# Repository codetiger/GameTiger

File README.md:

</p>

## About GameTiger Console
A retro-themed gaming console, crafted and tailored exclusively for educational enjoyment. The console boasts a custom-designed printed circuit board (PCB), meticulously created entirely from the ground up, and is centered around the remarkable RP2040 MCU chip. The primary objective of this endeavor is to maintain complete openness, facilitating the exploration of electronic PCB design and the establishment of a platform that fosters the creation of games and emulators on microcontrollers.

<div style="display: flex; justify-content: space-between;">

</div>

## Games
|   |   |
|---|---|
| Snake | 2048 |
|  |  
| Tetris | Minesweeper |
|  | 
| Tic Tac Toe | Ninja Frog |
|  | 

## Software
The software is constructed using the Pico C++ SDK, incorporating essential hardware interfacing functionalities. As an illustration, the well-known Snake game is already available. The following modules are currently available and are continually being developed.

* Operating System Drivers
    * Display driver
    * Button interrupts
    * Battery management system driver
* Framebuffer Library
    * Supports transparency
    * Streaming to display memory using DMA
    * Draw primitives (Line, Rect, Fill Rect)
    * Supports drawing images with alpha channel
* Sprite sheet 
    * Support for sprite sheet 
    * Basic tilemap support
* Font system based on Sprite sheet
* Menu system
    * Games
    * Hardware config
        * Display brightness
        * Display sleep time after inactivity

The software is well optimised to achieve a target of 30 frames per second. The Snake game achieves more than 44 FPS on a default settings without overclocking. 

Hardware V3:

Hardware V2:

Hardware V1:

## Build your favourite games
If you're looking to contribute to the project by developing your own games for the GameTiger console, please refer to our developer guide for detailed instructions.
[Developer's Guide](docs/dev_guide.md)

## To Do
* Add more games
* Design Case in CAD software for 3d printing

## License
The entire project is open-sourced software licensed under the MIT license.

## References
* [Hardware Design with RP2040](https://datasheets.raspberrypi.com/rp2040/hardware-design-with-rp2040.pdf)
* [Minimal RP2040 Board](http://www.technoblogy.com/show?3U75)
* [HAGL Graphics Library](https://github.com/tuupola/hagl)
* [PCB Design for RP2040 youtube video](https://www.youtube.com/watch?v=kcwvuwetgEQ)

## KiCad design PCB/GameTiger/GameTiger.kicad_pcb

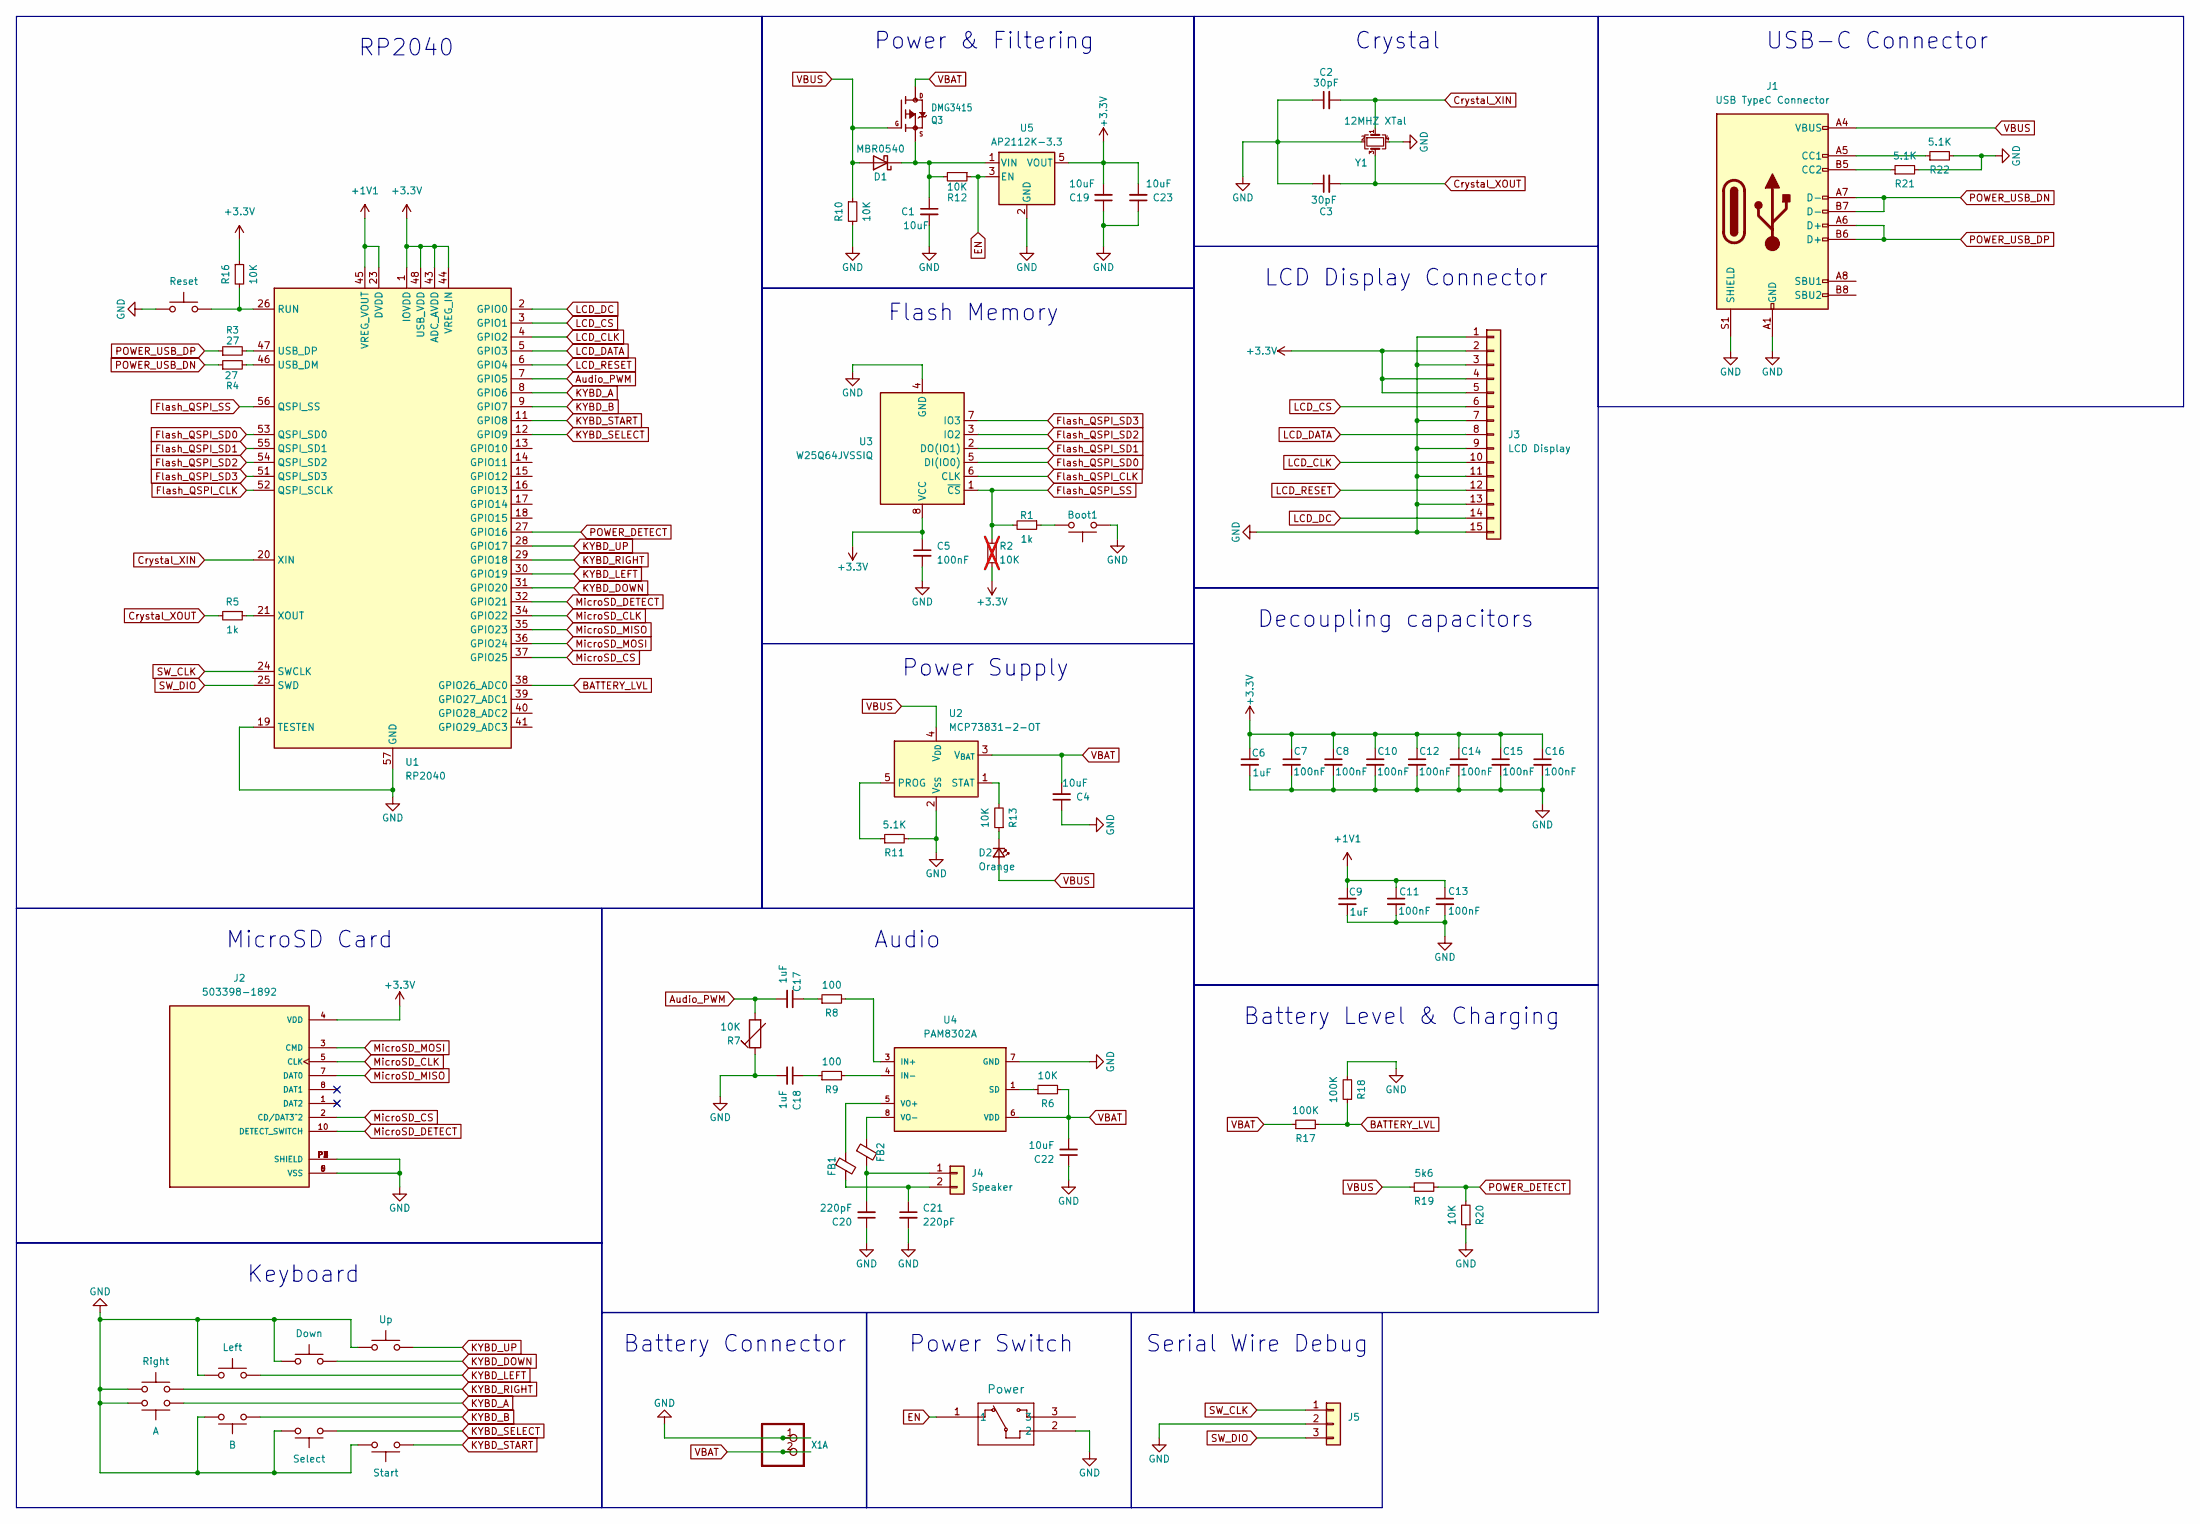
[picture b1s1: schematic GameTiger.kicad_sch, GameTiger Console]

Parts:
A1: A; SW_PUSH-12mm_3DModel; LCSC C411882
B1: B; SW_PUSH-12mm_3DModel; LCSC C411882
Boot1: Boot; SW_SPST_B3U-1000P; Mfr.Part # B3U-1000P; LCSC C231329
C1, C4, C19, C22, C23: 10uF; C_0805_2012Metric; LCSC C15850
C2, C3: 30pF; C_0402_1005Metric; LCSC C1570
C5, C7, C8, C10, C11, C12, C13, C14, C15, C16: 100nF; C_0402_1005Metric; LCSC C1525
C6, C9, C17, C18: 1uF; C_0402_1005Metric; LCSC C52923
C20, C21: 220pF; C_0805_2012Metric; LCSC C107145
D1: MBR0540; D_SOD-123; Manuf. Part # MBR0540; LCSC C116159
D2: Orange; LED_0402_1005Metric; LCSC C965791
Down1: Down; SW_PUSH-12mm_3DModel; LCSC C411882
FB1, FB2: FerriteBead_Small; Ferrite_0805_2012Metric; Manuf. Part # BLM21BD102SN1D; LCSC C85835
J1: USB TypeC Connector; USB_C_Receptacle_HRO_TYPE-C-31-M-12; Manuf. Part # GT-USB-7010ASV; LCSC C2988369
J2: 503398-1892; MOLEX_503398-1892; Manuf. Part # 5033981892; LCSC C428492
J3: LCD Display; TE_1-1734839-5_1x15-1MP_P0.5mm_Horizontal; Manuf. Part # 1-1734839-5; LCSC C262209
J4: Speaker; SolderWire-0.5sqmm_1x02_P4.6mm_D0.9mm_OD2.1mm
J5: Conn_01x03; SolderWire-0.25sqmm_1x03_P4.2mm_D0.65mm_OD1.7mm
Left1: Left; SW_PUSH-12mm_3DModel; LCSC C411882
Power1: Power; MK-12C02-G020_GSW; Manuf. Part # MK-12C02-G020; LCSC C963206
Q3: DMG3415; SOT-23; Manuf. Part # DMG3415U-7; LCSC C96616
R1, R5: 1k; R_0402_1005Metric; LCSC C11702
R2: 10K; R_0402_1005Metric; LCSC C25744; not fitted
R3, R4: 27; R_0402_1005Metric; LCSC C25190
R6, R10, R12, R13, R16, R20: 10K; R_0402_1005Metric; LCSC C25744
R7: 10K; Potentiometer_Bourns_TC33X_Vertical; Manuf. Part # TC33X-2-103E; LCSC C719176
R8, R9: 100; R_0402_1005Metric; LCSC C25076
R11, R21, R22: 5.1K; R_0402_1005Metric; LCSC C25905
R17, R18: 100K; R_0402_1005Metric; LCSC C25741
R19: 5k6; R_0402_1005Metric; LCSC C25908
Reset1: Reset; SW_SPST_B3U-1000P; Mfr.Part # B3U-1000P; LCSC C231329
Right1: Right; SW_PUSH-12mm_3DModel; LCSC C411882
Select1: Select; SW_TH_Tactile_Omron_B3F-10xx; LCSC C411882
Start1: Start; SW_TH_Tactile_Omron_B3F-10xx; LCSC C411882
U1: RP2040; QFN-56-1EP_7x7mm_P0.4mm_EP3.2x3.2mm; Mfr.Part # RP2040; LCSC C2040
U2: MCP73831-2-OT; SOT-23-5; Manuf. Part # MCP73831T-2ACI/OT; LCSC C424093
U3: W25Q64JVSSIQ; SOIC-8_5.23x5.23mm_P1.27mm; Manuf. Part # W25Q64JVSSIQ; LCSC C179171
U4: PAM8302A; MSOP-8_3x3mm_P0.65mm; Manuf. Part # PAM8302AASCR; LCSC C113367
U5: AP2112K-3.3; SOT_RG1_DIO; Manuf. Part # AP2112K-3.3TRG1; LCSC C51118
Up1: Up; SW_PUSH-12mm_3DModel; LCSC C411882
X1: JST_PH_S2B-PH-SM4-TB_1x02-1MP_P2.00mm_Horizontal; Manuf. Part # S2B-PH-SM4-TB(LF)(SN); LCSC C295747
Y1: 12MHZ XTal; Crystal_SMD_3225-4Pin_3.2x2.5mm; Manuf. Part # X322512MSB4SI; LCSC C9002

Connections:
+1V1: C9.1, C11.1, C13.1, U1.23 (DVDD), U1.45 (VREG_VOUT), U1.50 (DVDD)
+3.3V: C5.1, C6.1, C7.1, C8.1, C10.1, C12.1, C14.1, C15.1, C16.1, C19.2, C23.2, J2.4 (VDD), J3.2, J3.4, J3.5, R2.1, R16.1, U1.1 (IOVDD), U1.10 (IOVDD), U1.22 (IOVDD), U1.33 (IOVDD), U1.42 (IOVDD), U1.43 (ADC_AVDD), U1.44 (VREG_IN), U1.48 (USB_VDD), U1.49 (IOVDD), U3.8 (VCC), U5.5 (VOUT)
Audio_PWM: C17.2, R7.2, U1.7 (GPIO5)
BATTERY_LVL: R17.2, R18.1, U1.38 (GPIO26_ADC0)
Crystal_XIN: C2.2, U1.20 (XIN), Y1.1
Crystal_XOUT: C3.2, R5.2, Y1.3
EN: Power1.1, R12.1, U5.3 (EN)
Flash_QSPI_CLK: U1.52 (QSPI_SCLK), U3.6 (CLK)
Flash_QSPI_SD0: U1.53 (QSPI_SD0), U3.5 (DI(IO0))
Flash_QSPI_SD1: U1.55 (QSPI_SD1), U3.2 (DO(IO1))
Flash_QSPI_SD2: U1.54 (QSPI_SD2), U3.3 (IO2)
Flash_QSPI_SD3: U1.51 (QSPI_SD3), U3.7 (IO3)
Flash_QSPI_SS: R1.2, R2.2, U1.56 (QSPI_SS), U3.1 (~CS)
GND: A1.2, B1.2, Boot1.1, C1.2, C2.1, C3.1, C4.1, C5.2, C6.2, C7.2, C8.2, C9.2, C10.2, C11.2, C12.2, C13.2, C14.2, C15.2, C16.2, C18.2, C19.1, C20.1, C21.2, C22.1, C23.1, Down1.1, J1.A1 (GND), J1.A12 (GND), J1.B1 (GND), J1.B12 (GND), J1.S1 (SHIELD), J2.6 (VSS), J2.9 (VSS), J2.P1 (SHIELD), J2.P2 (SHIELD), J2.P3 (SHIELD), J2.P4 (SHIELD), J3.1, J3.3, J3.7, J3.9, J3.11, J3.13, J3.15, J5.2, Left1.1, Power1.2, R7.1, R10.2, R11.2, R18.2, R20.1, R21.2, R22.2, Reset1.1, Right1.1, Select1.2, Start1.2, U1.19 (TESTEN), U1.57 (GND), U2.2 (V_{SS}), U3.4 (GND), U4.7 (GND), U5.2 (GND), Up1.1, X1.1, Y1.2, Y1.4
KYBD_A: A1.1, U1.8 (GPIO6)
KYBD_B: B1.1, U1.9 (GPIO7)
KYBD_DOWN: Down1.2, U1.31 (GPIO20)
KYBD_LEFT: Left1.2, U1.30 (GPIO19)
KYBD_RIGHT: Right1.2, U1.29 (GPIO18)
KYBD_SELECT: Select1.1, U1.12 (GPIO9)
KYBD_START: Start1.1, U1.11 (GPIO8)
KYBD_UP: U1.28 (GPIO17), Up1.2
LCD_CLK: J3.10, U1.4 (GPIO2)
LCD_CS: J3.6, U1.3 (GPIO1)
LCD_DATA: J3.8, U1.5 (GPIO3)
LCD_DC: J3.14, U1.2 (GPIO0)
LCD_RESET: J3.12, U1.6 (GPIO4)
MicroSD_CLK: J2.5 (CLK), U1.34 (GPIO22)
MicroSD_CS: J2.2 (CD/DAT3^2), U1.37 (GPIO25)
MicroSD_DETECT: J2.10 (DETECT_SWITCH), U1.32 (GPIO21)
MicroSD_MISO: J2.7 (DAT0), U1.35 (GPIO23)
MicroSD_MOSI: J2.3 (CMD), U1.36 (GPIO24)
unnamed: Boot1.2, R1.1
unnamed: C17.1, R8.1
unnamed: C18.1, R9.1
unnamed 35: C1.1, D1.1 (K), R12.2, U5.1 (VIN); also elsewhere on the board
unnamed: D2.1 (K), R13.1
unnamed: J1.A5 (CC1), R22.1
unnamed: J1.B5 (CC2), R21.1
unnamed: C20.2, FB2.2, J4.1
unnamed: C21.1, FB1.2, J4.2
unnamed: R16.2, Reset1.2, U1.26 (RUN)
unnamed: R4.2, U1.46 (USB_DM)
unnamed: R3.2, U1.47 (USB_DP)
unnamed: R5.1, U1.21 (XOUT)
unnamed: R11.1, U2.5 (PROG)
unnamed: R13.2, U2.1 (STAT)
unnamed: R8.2, U4.3 (IN+)
unnamed: R9.2, U4.4 (IN-)
unnamed: R6.1, U4.1 (SD)
unnamed: FB1.1, U4.5 (VO+)
unnamed: FB2.1, U4.8 (VO-)
POWER_DETECT: R19.2, R20.2, U1.27 (GPIO16)
POWER_USB_DN: J1.A7 (D-), J1.B7 (D-), R4.1
POWER_USB_DP: J1.A6 (D+), J1.B6 (D+), R3.1
SW_CLK: J5.1, U1.24 (SWCLK)
SW_DIO: J5.3, U1.25 (SWD)
VBAT: C4.2, C22.2, R6.2, R17.1, U2.3 (V_{BAT}), U4.6 (VDD), X1.2; also elsewhere on the board
VBUS: D1.2 (A), D2.2 (A), J1.A4 (VBUS), J1.A9 (VBUS), J1.B4 (VBUS), J1.B9 (VBUS), R10.1, R19.1, U2.4 (V_{DD}); also elsewhere on the board

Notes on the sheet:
Serial Wire Debug
Battery Connector
Audio
Battery Level & Charging
RP2040
Power Switch
Keyboard
Decoupling capacitors
MicroSD Card
Power Supply
LCD Display Connector
Power & Filtering
Crystal
Flash Memory
USB-C Connector

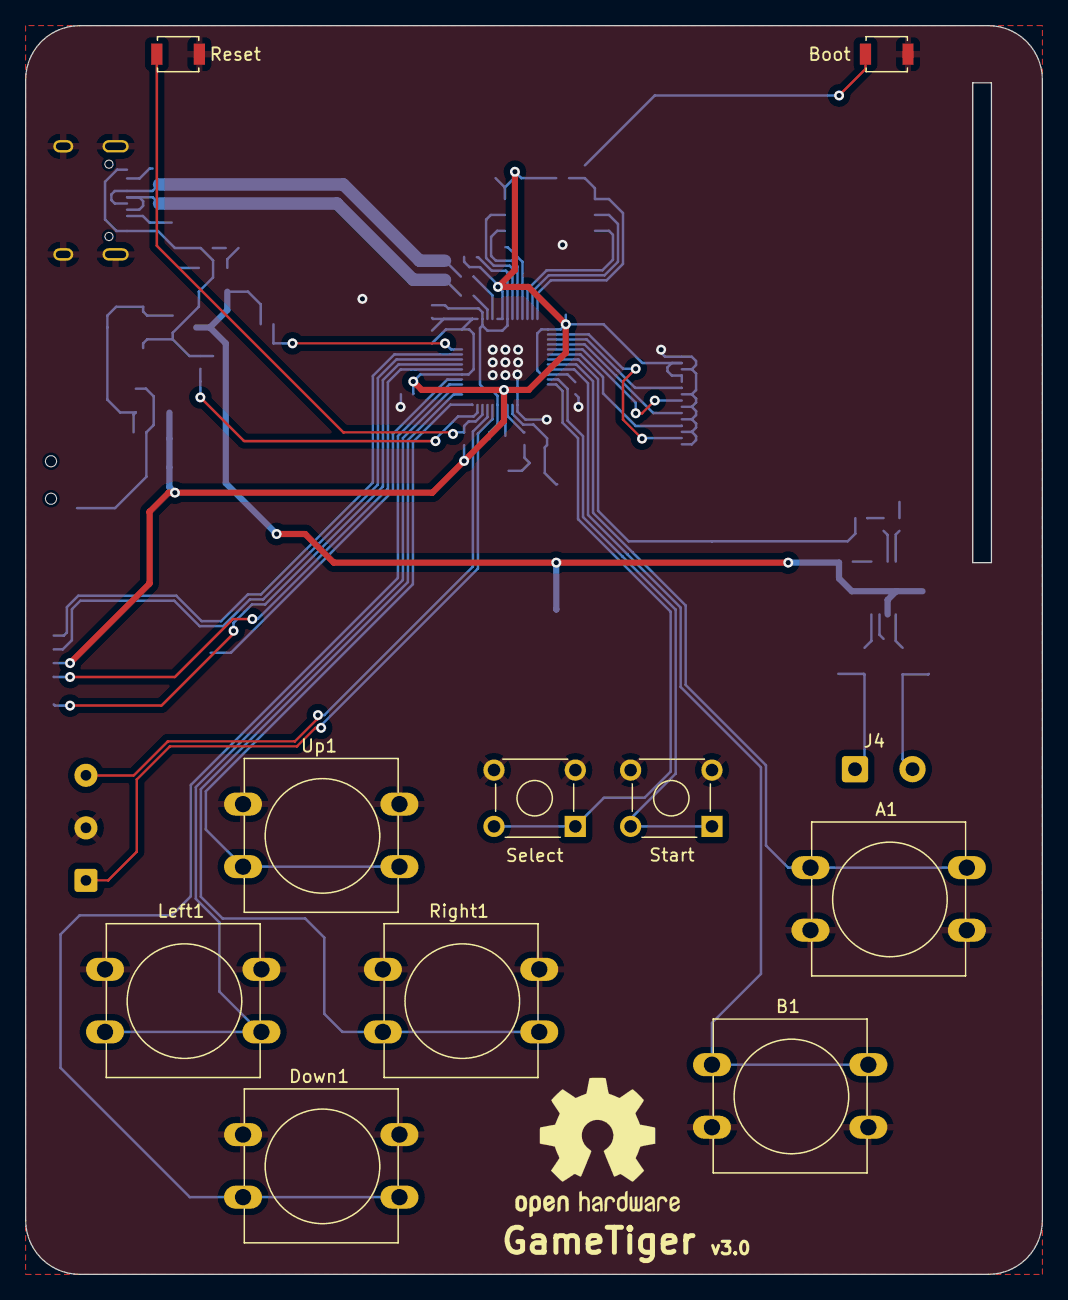
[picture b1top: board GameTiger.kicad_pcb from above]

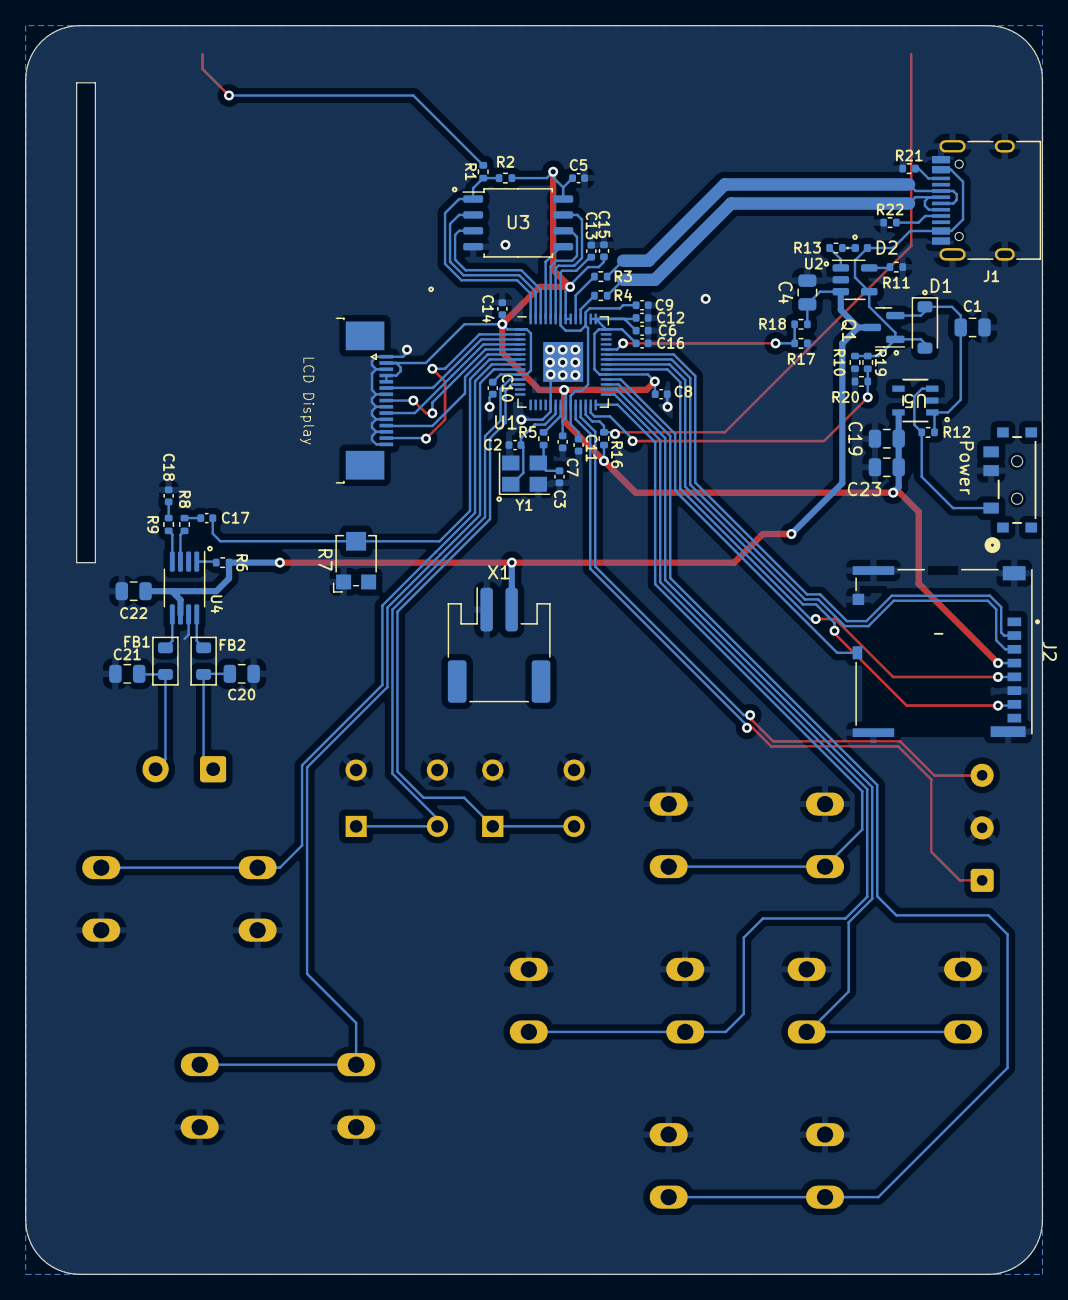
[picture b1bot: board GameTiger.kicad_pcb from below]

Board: 2 copper layers, 81.3 x 99.8 mm, 71 parts (59 on the bottom side), 59 nets.

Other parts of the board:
Q1: DMG3415; SOT-23

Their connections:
unnamed 35: Q1.2 (S); also elsewhere on the board
VBAT: Q1.3 (D); also elsewhere on the board
VBUS: Q1.1 (G); also elsewhere on the board

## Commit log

2022-02-18 Initial Commit with Snake game working
2022-02-18 Fixed support for MacOS
2022-03-08 Added splash, menu and game screen with Snake Game working
2022-03-08 Performance optimisations on image rendering
2022-03-09 Display class performance optimisation. FPS improved from 12 to 22
2022-03-09 Added more info on readme file
2022-03-09 Reduced the image size
2022-03-14 Fixed highscore persistance
2022-03-14 Release UF2 files for direct installation
2022-03-16 added ingame speed config using buttons a/b
2022-03-26 Added 2048 game
2022-03-27 Added support to run on computers for quicker development of games
2022-03-29 1. Added Tetris game. 2. Cleaned time calculations. 3. Improved visuals for 2048.
2022-03-29 1. Added smooth splash screen. 2. Fixed gameplay issue in Tetris
2022-03-29 Fixed random seed to main function
2022-03-29 Added Minesweeper game
2022-03-29 Added games list in the README file
2022-03-30 1. Fixed crash issue on Pico. 2. Improved image loading. 3. added Settings and About menu item to be filled later
2022-03-30 Added GameOver screen in 2048 as suggested by Naethraa
2022-03-31 1. Added Tic Tac Toe game. 2. Menu selection stays in prev mode when coming back from a game.
2022-04-01 Added Minimax based AI for Tic Tac Toe
2022-04-02 Randomised the minimax moves for computer user
2022-04-02 1. Changed Tetris to soft colors. 2. Randomised AI movements to avoid repeated stratergy.
2022-04-02 Fixed quick drop issue in 2048 instead of Tetris
2022-04-07 1. Added support for Tilemap\n 2. Menu, and Splash screens now use tilemap
2022-04-09 1. Added options in the menu. 2. Difficulty level in Tetris, and Minesweeper games
2022-04-09 1. Added difficulty for TicTacToe game AI
2022-04-09 1. Added Settings and About menu. 2. Fixed the use of screenid during back button press. 3. Added New font support
2022-04-10 1. Added support for animated tilemap. 2. Increased size of bg tiles in about menu to speedup
2022-04-11 1. Added Pixel Adventure basic tilemap.
2022-04-11 1. Removed old fonts and replaced with scalable font.
2022-04-12 Added LevelMap class with game items
2022-04-14 1. Added Ninja Frog to the menu. 2. Fixed issues in Level Map and other screens.
2022-04-15 Added support for Image/Sprite Flip horizontal and vertical
2022-04-17 Sprite packer python script updated for NinjaFrog game tiles
2022-04-19 Reduced images to 2 sprites for all games
2022-04-19 Cleanedup map usage in images to reduce memory usage.
2022-04-19 Added pause feature for Snake, G2048 and Tetris games
2022-04-21 Optimised image generation and drawing with changes in Color struct
2022-04-22 Added support for Indexed color with alpha and non indexed in Image class. 2. No-Alpha Image drawing uses DMA for rows
2022-04-23 Added Enemy movement for mushroom
2022-04-23 Fixed DMA crash issue on drawing sprite
2022-04-23 Added Gif animation in README
2022-04-24 Added Hero movements
2022-04-25 Fully working Ninja Frog game movement physics
2022-04-25 Added support for oneway tile collision
2022-04-26 Added support for creating levels in Tiled editor
2022-04-26 Updated ReadMe file with animated GIF for games
2022-04-27 Added support for Nearest Neighbor scaling
2022-04-27 Fixed issue in scaling. Added smooth scaling and alpha effect in menu screen
2022-04-28 Added support for Sound effects
2022-04-29 Fixed issues in other platforms related to Audio controller
2022-04-29 Removed temp images
2022-04-29 Added Pos2, Size2, and Rect2 structs for easy
2022-04-30 Added new level in Ninja Frog game
2022-05-01 Renamed Pos2 to Vec2. Added support for drawing triangles
2022-05-12 Added software 3d rendering engine. Fixed out of screen image drawing issue: Signed int conversion issue
2022-05-12 Fixed texture coordinates interpolation issue for int16_t
2022-05-12 Added support for optional perspective correction in models. Fixed texture interpolation issue. Added depthbuffer support with 8bit depth buffer
2023-04-14 Code clean up, bug fixes
2023-05-14 Moved to Adafruit Feather RP2040 and PCF8575 for keypad to save GPIO
2023-05-14 Fixed Battery level detection issue
2023-05-23 Added new Lora driver
2023-05-23 Log format fix
2023-06-05 Messaging working successfully over LoRa SX1262. Added Code for Xiao for message server
2023-06-18 Fixed LoRa messaging
2023-06-22 1. Added GameBoy Emulator. 2. CPU Overclocking
2023-06-23 Added more games, Added support for color
2023-06-24 Minor changes in code, and documents
2023-06-25 Switched to SPI mode 3 to gain 10% better frame rate
2023-06-26 Code cleanup with DMA variable name more readable
2023-06-27 Added FrameBuffer class to clean up Display class
2023-06-28 Added clean framebuffer class
2023-06-29 Issue in multiple DMA draw, as it ends up in race condition. Falling back to blocking DMA calls
2023-07-01 Cleaned up Framebuffer and optimised setPixel function
2023-07-26 Added basic Schematics for new version
2023-07-30 PCB Schematic for V2.0 is completed
2023-08-01 Updated Schematics to correct footprints
2023-08-06 PCB layout completed with all tracks and connections
2023-08-08 Added more details on the PCB components
2023-08-08 PCB layout and component reference completed
2023-08-08 Ready for uploading to JLCPCB
2023-08-11 Added battery level and charge detect connectors
2023-08-15 Completed updating the PCB design for peer review
2023-08-16 Fixed differential pairs for USB-C connection
2023-08-17 Updated PCB design with some improvements in differential pair for USB
2023-08-18 Redesigned pcb layout to fix errors in decoupling caps and ground plane
2023-08-19 PCB Design track cleanup
2023-08-19 Added reference link for PCB design, fixed differential pair routes and uncut GND plane on the other side
2023-08-19 Minor fixes in PCB design
2023-08-20 PCB design completed and ordered for fab
2023-10-16 Updated code and configurations for new hardware
2024-01-17 Upgraded Peanut-GB emulator. Fixed some compilation issues.
2024-01-20 Updated the README file
2024-01-26 Added Blender file for 3D printing Case
2024-01-27 3D Case geometry file ready for printing prototype
2024-04-01 Added getting started guide for developers and organized docs.
2024-04-03 Repo reset
2024-08-17 Upgraded SDK version, added acrylic case
2024-08-18 Fixed issue with new SDK version and removed SDL implementation
